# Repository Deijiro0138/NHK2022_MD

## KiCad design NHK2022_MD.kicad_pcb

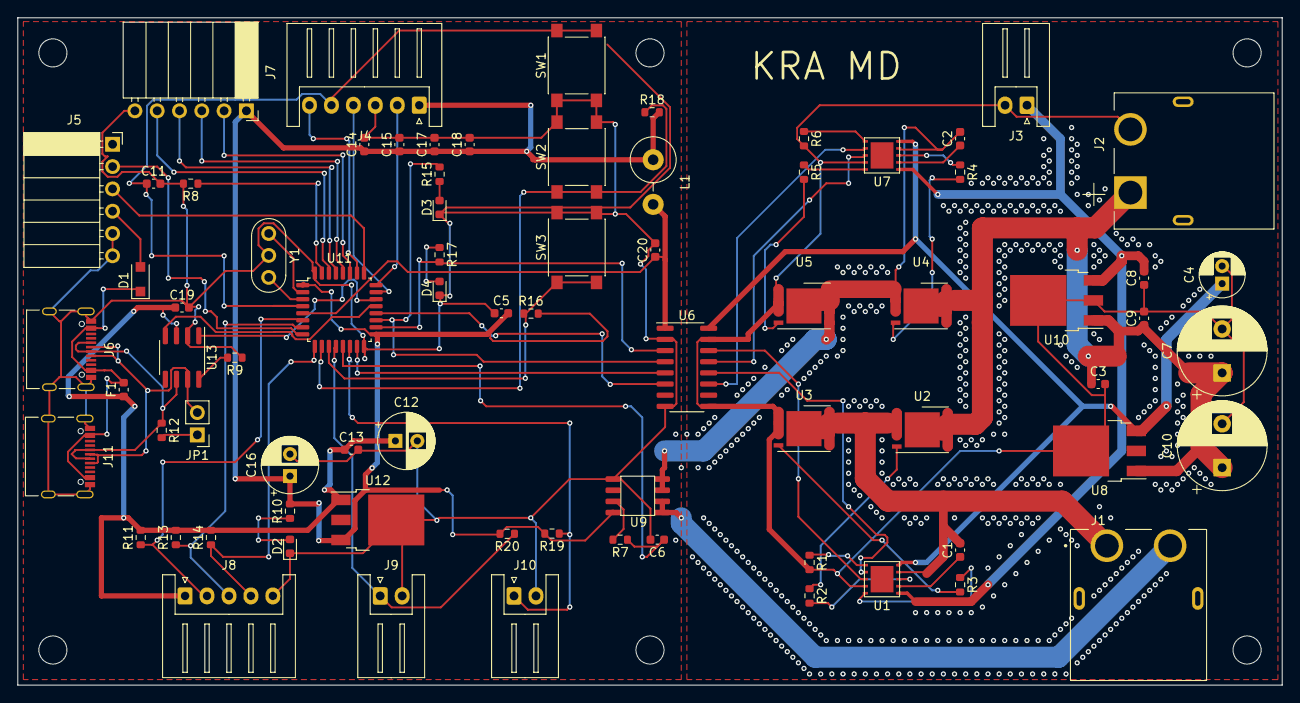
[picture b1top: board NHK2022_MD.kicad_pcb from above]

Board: 2 copper layers, 144.0 x 76.0 mm, 81 parts (0 on the bottom side), 64 nets.

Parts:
C1, C2: 0.068u; C_0603_1608Metric
C3, C9: 0.33u; C_0603_1608Metric
C4: 22u; CP_Radial_D5.0mm_P2.00mm
C5, C8, C11, C13, C14, C15, C17, C18, C19: 0.1u; C_0603_1608Metric
C6: 0.02u; C_0603_1608Metric
C7, C10: 470u; CP_Radial_D10.0mm_P5.00mm
C12, C16: 47u; CP_Radial_D6.3mm_P2.50mm
C20: 10u; C_0603_1608Metric
D1: D; D_SOD-123F
D2, D3, D4: LED; LED_0603_1608Metric
F1: Polyfuse 1A; Fuse_0603_1608Metric
J1: XT60PW-F; AMASS_XT60PW-F
J2: XT60PW-M; AMASS_XT60PW-M
J3: XH; JST_XH_S2B-XH-A_1x02_P2.50mm_Horizontal
J4: Conn_01x06_Female; JST_XH_S6B-XH-A_1x06_P2.50mm_Horizontal
J5: Conn_01x06_Female; PinSocket_1x06_P2.54mm_Horizontal
J6, J11: USB_C_Receptacle_USB2.0; USB_C_Receptacle_Palconn_UTC16-G
J7: Conn_01x06; PinSocket_1x06_P2.54mm_Horizontal
J8: Conn_01x05; JST_XH_S5B-XH-A_1x05_P2.50mm_Horizontal
J9, J10: Conn_01x02; JST_XH_S2B-XH-A_1x02_P2.50mm_Horizontal
JP1: Jumper_2_Open; PinHeader_1x02_P2.54mm_Vertical
L1: INDUCTOR; L_Axial_L12.0mm_D5.0mm_P5.08mm_Vertical_Fastron_MISC
MH1, MH2, MH3, MH4, MH5, MH6: MountingHole_3.2mm_M3
R1, R6: 100k; R_0603_1608Metric
R2, R3, R4, R5: 13; R_0603_1608Metric
R7: 100; R_0603_1608Metric
R8, R9, R11, R13, R14, R16, R18: 10K; R_0603_1608Metric
R10, R15, R17: 1k; R_0603_1608Metric
R12: 120; R_0603_1608Metric
R19, R20: 1K; R_0603_1608Metric
SW1, SW2, SW3: SW_MEC_5E; Button_switch
U1, U7: HIP2210FRTZ-T7A
U2, U3, U4, U5: AONS32304
U6: MAX14930DASE+
U8, U12: BA33BC0FP; TO-252-3_TabPin4
U9: CC6920BSO-50A
U10: NJM7812SDL; NJM7812SDL1
U11: STM32F303K8Tx; LQFP-32_7x7mm_P0.8mm
U13: MCP2551-I-SN; SOIC-8_3.9x4.9mm_P1.27mm
Y1: 8MHz; Resonator-3Pin_W8.0mm_H3.5mm

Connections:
+3.3VADC: C20.1, L1.2, U6.1, U11.5
+3V3: C5.2, C14.1, C15.1, C16.1, C17.1, C18.1, J4.1, J7.1, L1.1, R10.2, R16.2, R18.2, R19.2, R20.2, U9.8, U11.1, U11.17, U12.3
+5V: C12.1, C13.1, C19.1, F1.1, J8.1, R11.2, R13.2, R14.2, U12.1, U13.3
+BATT: C3.1, C7.1, C9.1, C10.1, J2.1, U2.3, U4.3, U8.1, U10.1
/CURRENT: C6.1, R7.1, U11.13
/EN1: U6.5, U11.15
/EN1_OUT: U1.7, U6.12
/EN2: U6.6, U11.20
/EN2_OUT: U6.11, U7.7
/GVIN: C8.2, J3.1, U1.1, U7.1, U10.3
/IP+: J1.2, U9.1, U9.2
/IP-: C2.2, U4.1, U5.3, U7.4, U9.3, U9.4
/NHK2022_MD_CTR/CANH: J6.A6, J6.B6, J11.A6, J11.B6, JP1.2, U13.7
/NHK2022_MD_CTR/CANL: J6.A7, J6.B7, J11.A7, J11.B7, R12.1, U13.6
/NHK2022_MD_CTR/CAN_RX: U11.21, U13.4
/NHK2022_MD_CTR/CAN_TX: U11.22, U13.1
/NHK2022_MD_CTR/ENC_A: J8.2, R11.1, U11.6
/NHK2022_MD_CTR/ENC_B: J8.3, R13.1, U11.7
/NHK2022_MD_CTR/ENC_Z: J8.4, R14.1, U11.9
/NHK2022_MD_CTR/LIM1: J9.1, R20.1, U11.12
/NHK2022_MD_CTR/LIM2: J10.1, R19.1, U11.14
/NHK2022_MD_CTR/NRST: C11.1, J4.5, SW1.3, SW1.4, U11.4
/NHK2022_MD_CTR/PB4: J7.2, U11.27
/NHK2022_MD_CTR/PB5: J7.3, U11.28
/NHK2022_MD_CTR/PB6: J7.4, U11.29
/NHK2022_MD_CTR/PB7: J7.5, U11.30
/NHK2022_MD_CTR/RUN_A: R18.1, SW2.1, SW2.2, U11.10
/NHK2022_MD_CTR/RUN_B: R16.1, SW3.1, SW3.2, U11.11
/NHK2022_MD_CTR/SWCLK: J4.2, U11.24
/NHK2022_MD_CTR/SWDIO: J4.4, U11.23
/NHK2022_MD_CTR/SWO: J4.6, U11.26
/NHK2022_MD_CTR/UART_5V: D1.1, F1.2, J6.A4, J6.A9, J6.B4, J6.B9, J11.A4, J11.A9, J11.B4, J11.B9
/NHK2022_MD_CTR/UART_RX: J5.3, U11.25
/NHK2022_MD_CTR/UART_TX: J5.2, U11.8
/PWM1: R17.2, U6.3, U11.18
/PWM1_OUT: U1.8, U6.14
/PWM2: R15.2, U6.4, U11.19
/PWM2_OUT: U6.13, U7.8
/VREF: C4.1, U1.5, U6.16, U7.5, U8.3
GND: C5.1, C6.2, C11.2, C12.2, C13.2, C14.2, C15.2, C16.2, C17.2, C18.2, C19.2, C20.2, D2.1, D3.1, D4.1, J4.3, J5.5, J5.6, J6.A1, J6.A12, J6.B1, J6.B12, J6.S1, J7.6, J8.5, J9.2, J10.2, J11.A1, J11.A12, J11.B1, J11.B12, J11.S1, R8.2, R9.1, SW1.1, SW1.2, SW2.3, SW2.4, SW3.3, SW3.4, U6.2, U6.8, U9.5, U11.16, U11.32, U12.4, U13.2, Y1.2
GNDPWR: C3.2, C4.2, C7.2, C8.1, C9.2, C10.2, J2.2, J3.2, R1.2, R6.2, U1.9, U3.1, U5.1, U6.9, U6.15, U7.9, U8.4, U10.2
unnamed: C1.1, U1.2
unnamed: C1.2, J1.1, U1.4, U2.1, U3.3
unnamed: C2.1, U7.2
unnamed: D1.2, J5.4
unnamed: D2.2, R10.1
unnamed: D3.2, R15.1
unnamed: D4.2, R17.1
unnamed: JP1.1, R12.2
unnamed: R1.1, U1.6
unnamed: R2.1, U2.2
unnamed: R2.2, U1.3
unnamed: R3.1, U1.10
unnamed: R3.2, U3.2
unnamed: R4.1, U7.3
unnamed: R4.2, U4.2
unnamed: R5.1, U7.10
unnamed: R5.2, U5.2
unnamed: R6.1, U7.6
unnamed: R7.2, U9.7
unnamed: R8.1, U11.31
unnamed: R9.2, U13.8
unnamed: U11.2, Y1.1
unnamed: U11.3, Y1.3
